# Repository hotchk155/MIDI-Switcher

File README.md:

The old project. Check MIDI-Switcher-2 for new one

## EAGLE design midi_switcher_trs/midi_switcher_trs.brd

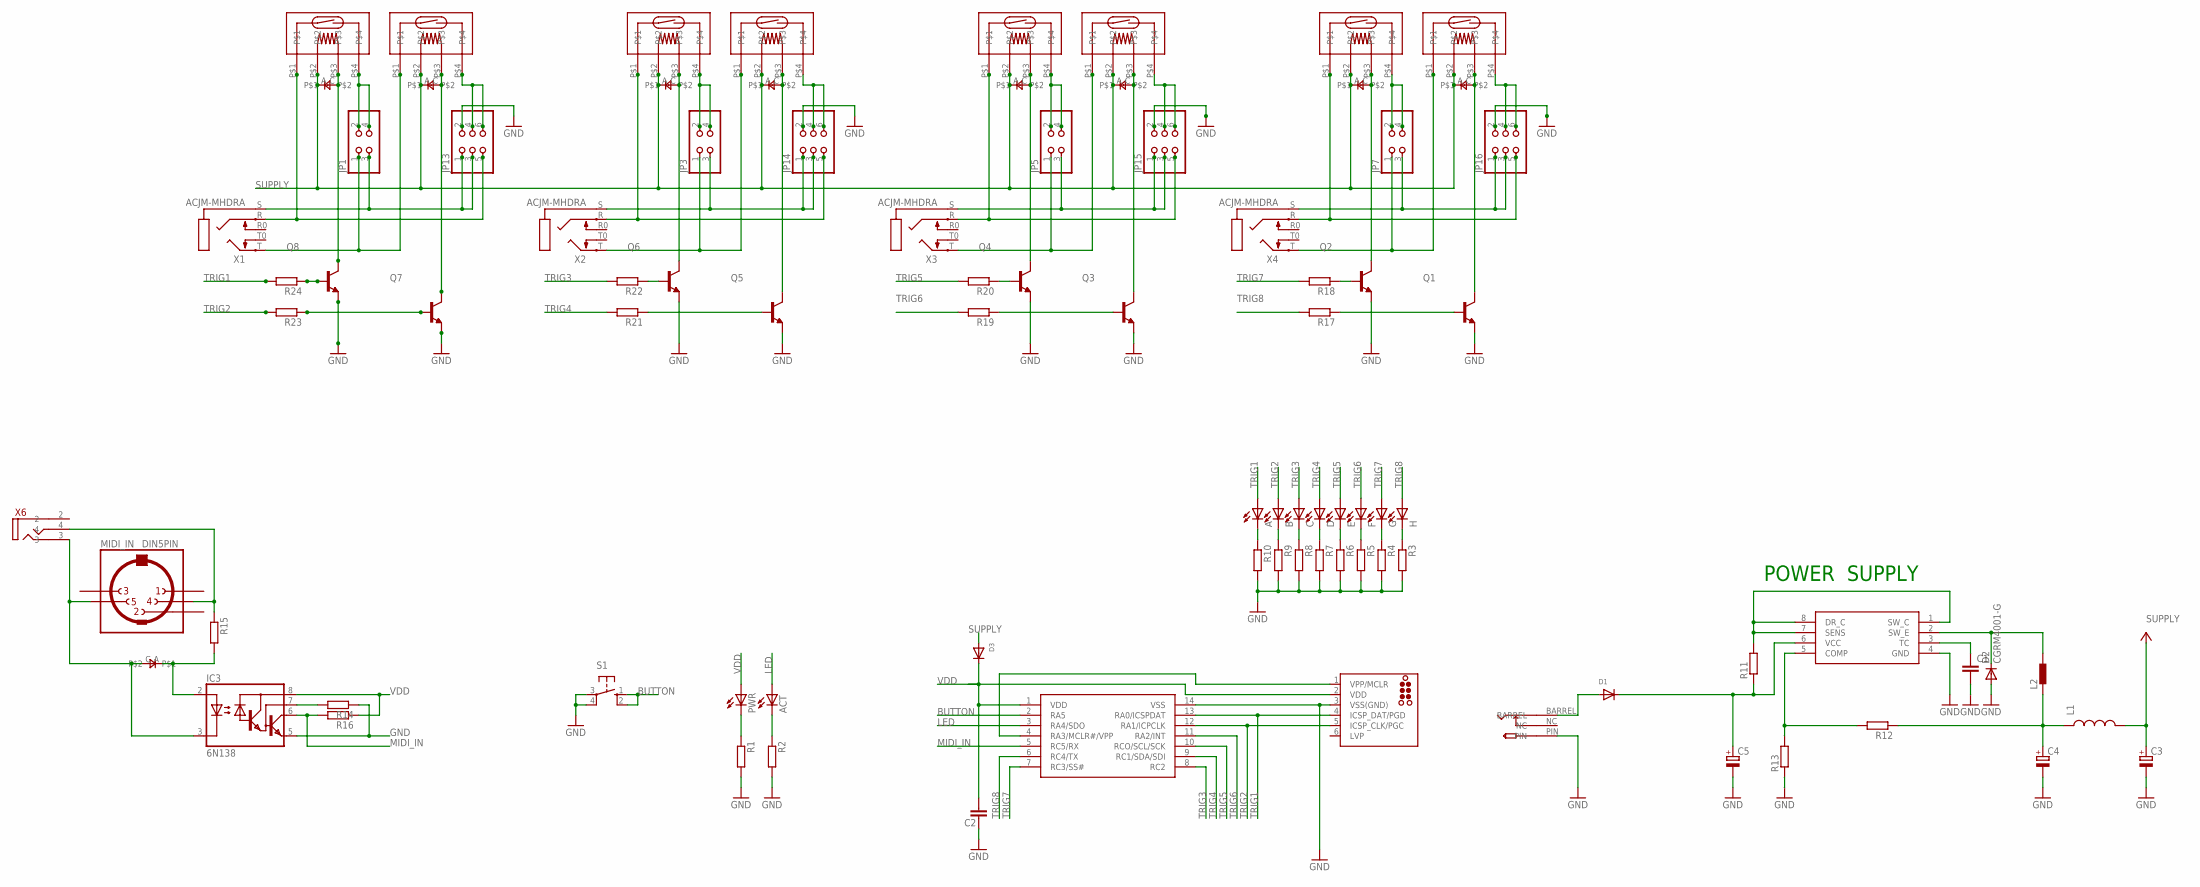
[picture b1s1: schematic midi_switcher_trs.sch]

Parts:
A: LED3MM
ACT: LED3MM
B: LED3MM
C: LED3MM
C1, C2: C-EUC0805; C0805
C3, C4, C5: CPOL-EUE2.5-7; E2,5-7
D: LED3MM
D1, D3: DIODESOD-123; SOD-123
D2: CGRM4001-G; SOD-123_MINI-SMA
D4, D5, D6, D7, D8, D9, D10, D11, D12: 0805DIODE
E: LED3MM
F: LED3MM
G: LED3MM
H: LED3MM
IC1: SP34063A_BOOST_REG; SOIC8
IC2: PIC16F1825SO14; SO14
IC3: 6N138; DIL08
ICSP: TC2030-MCP-NL
JP1, JP3, JP5, JP7: PINHD-2X2; 2X02
JP13, JP14, JP15, JP16: PINHD-2X3; 2X03
L1: INDUCTOR1210; 1210
L2: DR1030
MIDI_IN: DIN5PIN; EDGEDIN
PWR: LED3MM
Q1, Q2, Q3, Q4, Q5, Q6, Q7, Q8: MMBT3904LT1-NPN-SOT23-BEC; SOT23-BEC
R1, R2, R3, R4, R5, R6, R7, R8, R9, R10, R11, R12, R13, R14, R15, R16, R17, R18, R19, R20, R21, R22, R23, R24: R-EU_R0805; R0805
RLY1, RLY2, RLY3, RLY4, RLY5, RLY6, RLY7, RLY8: 9007-REED-RELAY
S1: 10-XX; B3F-10XX
U$9: PWR_SOCKET_2_1MM
X1, X2, X3, X4: ACJM-MHDRA; ACJM-MHDR
X6: VERTICAL_3_5MM_SOCKET

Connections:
+9V: C5.+, D1.C, IC1.6 (VCC), R11.1
BUTTON: IC2.2 (RA5), S1.1 (S), S1.2 (S1)
GND: C1.2, C2.2, C3.-, C4.-, C5.-, D2.A, IC1.4 (GND), IC2.14 (VSS), IC3.5 (GND), ICSP.3 (VSS(GND)), JP13.2, JP14.2, JP15.2, JP16.2, Q1.E, Q2.E, Q3.E, Q4.E, Q5.E, Q6.E, Q7.E, Q8.E, R1.2, R2.2, R3.2, R4.2, R5.2, R6.2, R7.2, R8.2, R9.2, R10.2, R13.1, R14.1, S1.3, S1.4 (P1), U$9.PIN
LED: ACT.A, IC2.3 (RA4/SDO)
MIDI_IN: IC2.5 (RC5/RX), IC3.6 (VO), R16.2
unnamed: JP1.2, JP1.4, RLY1.P$4
unnamed: JP13.4, JP13.6, RLY2.P$4
unnamed: JP13.5, RLY1.P$1, X1.R (2)
unnamed: JP1.1, RLY2.P$1, X1.T (5)
unnamed: JP1.3, JP13.1, JP13.3, X1.S (1)
unnamed: D11.C, Q7.C, RLY2.P$3
unnamed: Q8.B, R24.1
unnamed: Q7.B, R23.1
unnamed: JP3.2, JP3.4, RLY3.P$4
unnamed: D12.C, Q8.C, RLY1.P$3
unnamed: JP14.4, JP14.6, RLY4.P$4
unnamed: JP14.5, RLY3.P$1, X2.R (2)
unnamed: JP3.1, RLY4.P$1, X2.T (5)
unnamed: JP3.3, JP14.1, JP14.3, X2.S (1)
unnamed: D10.C, Q6.C, RLY3.P$3
unnamed: D9.C, Q5.C, RLY4.P$3
unnamed: Q6.B, R22.1
unnamed: Q5.B, R21.1
unnamed: JP5.2, JP5.4, RLY5.P$4
unnamed: JP15.4, JP15.6, RLY6.P$4
unnamed: JP15.5, RLY5.P$1, X3.R (2)
unnamed: JP5.1, RLY6.P$1, X3.T (5)
unnamed: JP5.3, JP15.1, JP15.3, X3.S (1)
unnamed: D8.C, Q4.C, RLY5.P$3
unnamed: D7.C, Q3.C, RLY6.P$3
unnamed: Q4.B, R20.1
unnamed: Q3.B, R19.1
unnamed: JP16.4, JP16.6, RLY8.P$4
unnamed: JP7.2, JP7.4, RLY7.P$4
unnamed: JP16.5, RLY7.P$1, X4.R (2)
unnamed: JP7.1, RLY8.P$1, X4.T (5)
unnamed: JP7.3, JP16.1, JP16.3, X4.S (1)
unnamed: D6.C, Q2.C, RLY7.P$3
unnamed: D5.C, Q1.C, RLY8.P$3
unnamed: Q2.B, R18.1
unnamed: Q1.B, R17.1
unnamed: D4.C, IC3.3 (C), MIDI_IN.5, X6.3
unnamed: MIDI_IN.4, R15.1, X6.4
unnamed: D4.A, IC3.2 (A), R15.2
unnamed: IC3.7 (VB), R14.2
unnamed: PWR.K (C), R1.1
unnamed: D1.A, U$9.BARREL
unnamed: IC1.1 (SW_C), IC1.7 (SENS), IC1.8 (DR_C), R11.2
unnamed: C1.1, IC1.3 (TC)
unnamed: D2.C, IC1.2 (SW_E), L2.2
unnamed: IC1.5 (COMP), R12.2, R13.2
unnamed: ACT.K (C), R2.1
unnamed: A.K (C), R10.1
unnamed: B.K (C), R9.1
unnamed: C.K (C), R8.1
unnamed: D.K (C), R7.1
unnamed: E.K (C), R6.1
unnamed: F.K (C), R5.1
unnamed: G.K (C), R4.1
unnamed: H.K (C), R3.1
unnamed: C4.+, L1.1, L2.1, R12.1
SUPPLY: C3.+, D3.A, D5.A, D6.A, D7.A, D8.A, D9.A, D10.A, D11.A, D12.A, L1.2, RLY1.P$2, RLY2.P$2, RLY3.P$2, RLY4.P$2, RLY5.P$2, RLY6.P$2, RLY7.P$2, RLY8.P$2
TRIG1: A.A, IC2.13 (RA0/ICSPDAT), ICSP.4 (ICSP_DAT/PGD), R24.2
TRIG2: B.A, IC2.12 (RA1/ICPCLK), ICSP.5 (ICSP_CLK/PGC), R23.2
TRIG3: C.A, IC2.8 (RC2), R22.2
TRIG4: D.A, IC2.9 (RC1/SDA/SDI), R21.2
TRIG5: E.A, IC2.10 (RCO/SCL/SCK), R20.2
TRIG6: F.A, IC2.11 (RA2/INT), R19.2
TRIG7: G.A, IC2.7 (RC3/SS#), R18.2
TRIG8: H.A, IC2.6 (RC4/TX), R17.2
VDD: C2.1, D3.C, IC2.1 (VDD), IC3.8 (VCC), ICSP.2 (VDD), PWR.A, R16.1
VPP: IC2.4 (RA3/MCLR#/VPP), ICSP.1 (VPP/MCLR)

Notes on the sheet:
POWER SUPPLY

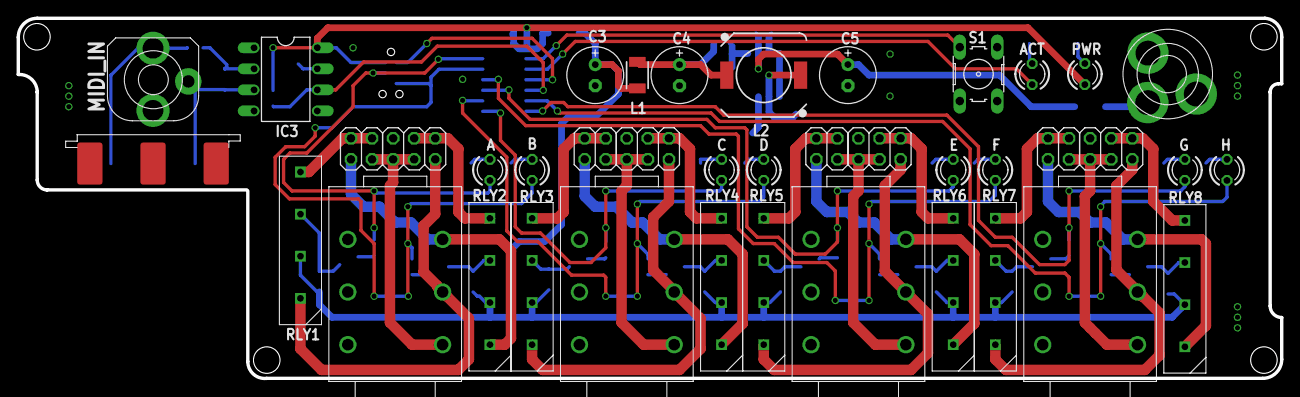
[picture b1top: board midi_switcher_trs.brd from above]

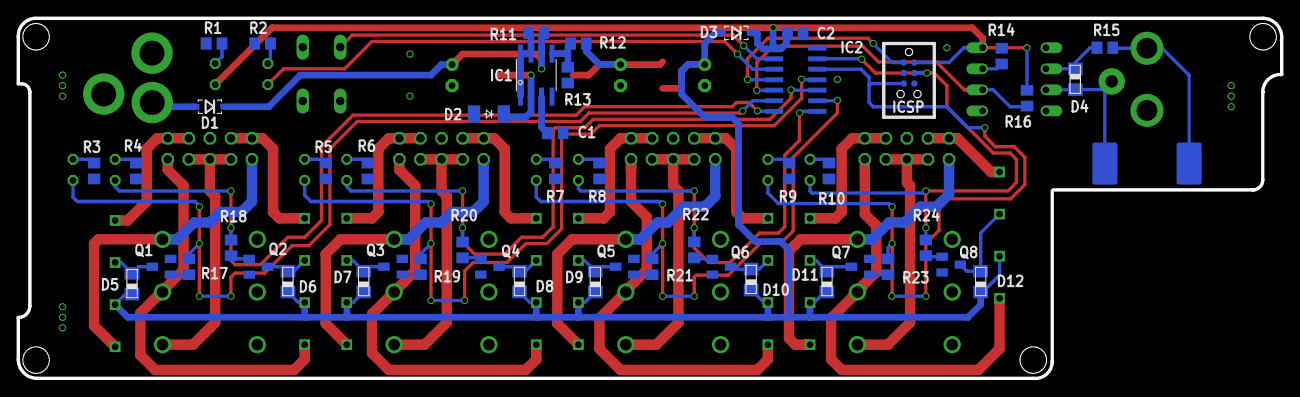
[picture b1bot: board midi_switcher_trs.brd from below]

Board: 2 copper layers, 152.4 x 43.4 mm, 89 parts (49 on the bottom side), 72 nets.

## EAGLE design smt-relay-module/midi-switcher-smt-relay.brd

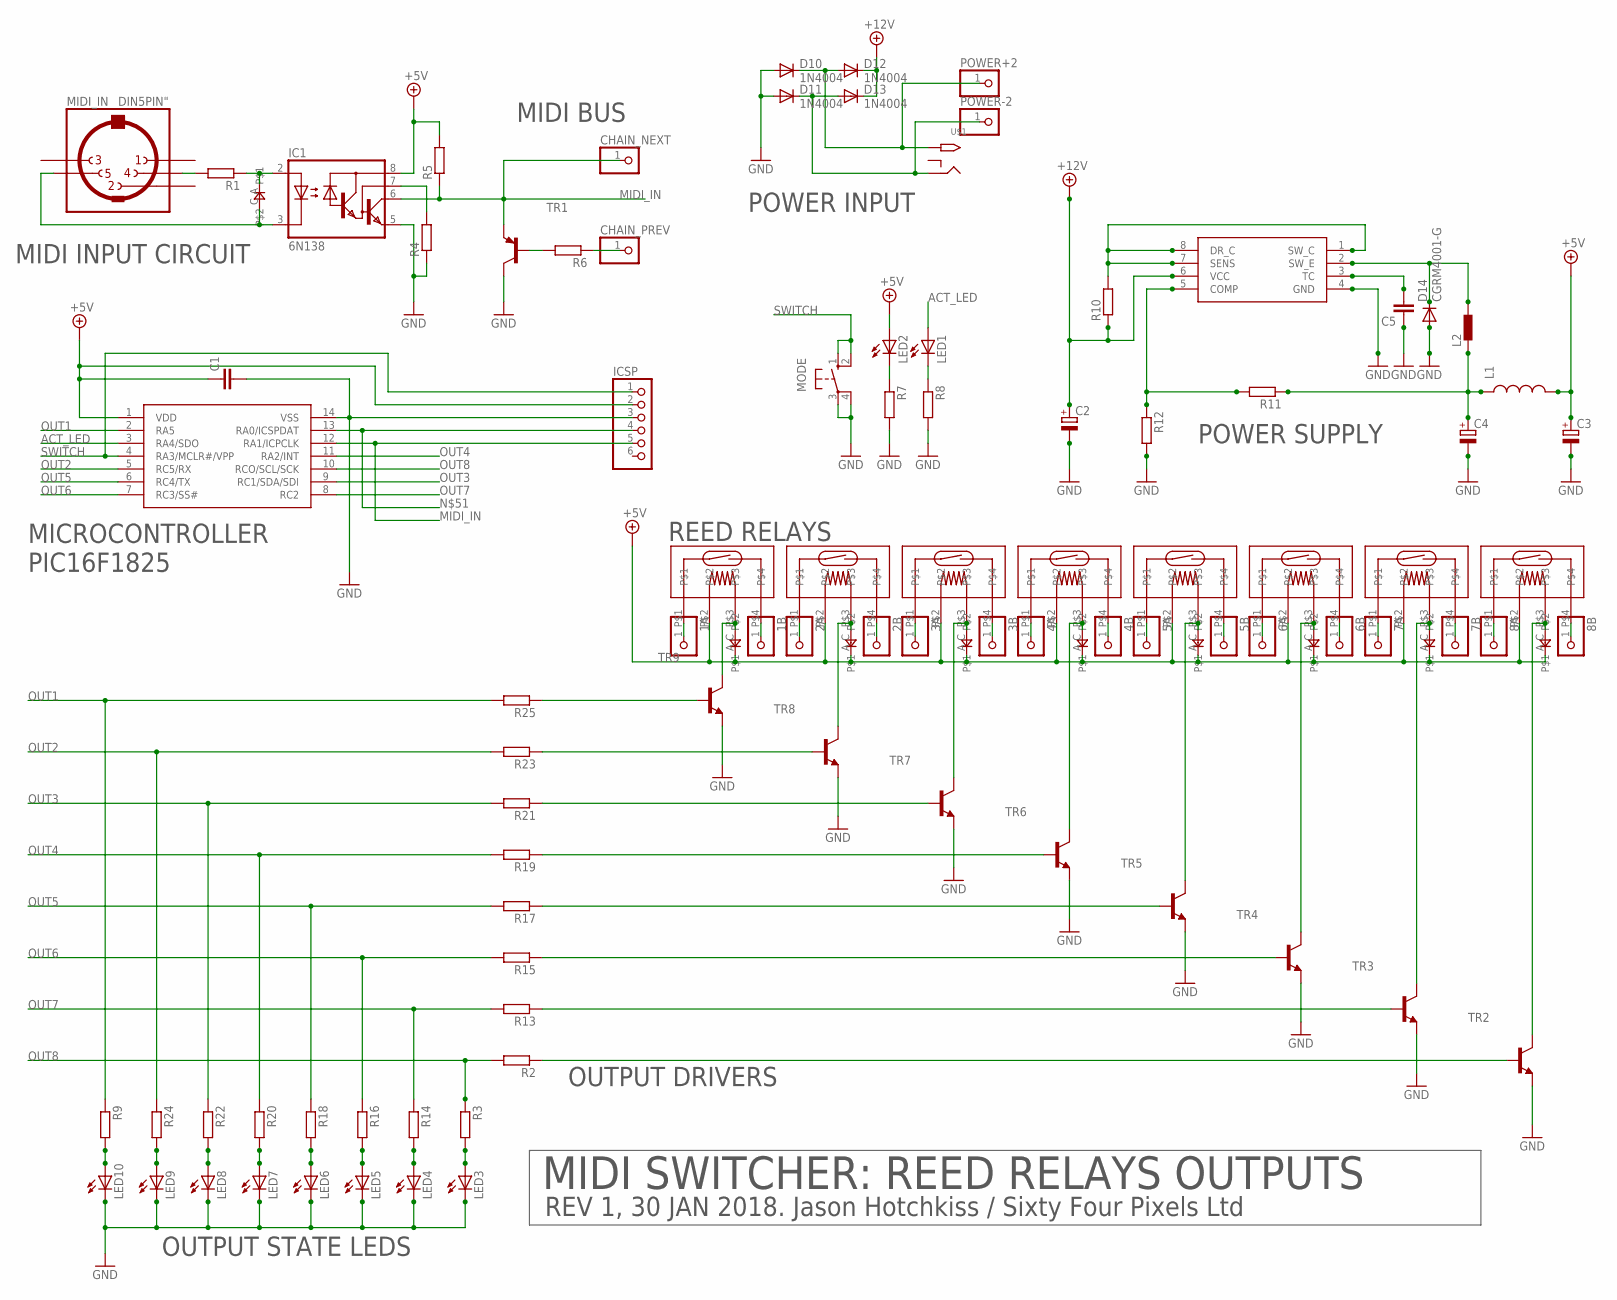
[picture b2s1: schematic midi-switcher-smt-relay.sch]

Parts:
1A, 1B, 2A, 2B, 3A, 3B, 4A, 4B, 5A, 5B, 6A, 6B, 7A, 7B, 8A, 8B: PINHD-1X1; 1X01
C1, C5: C-EUC0805; C0805
C2, C3, C4: CPOL-EUE2.5-7; E2,5-7
CHAIN_NEXT: PINHD-1X1; 1X01
CHAIN_PREV: PINHD-1X1; 1X01
D1, D2, D3, D4, D5, D6, D7, D8, D9: 0805DIODE
D10, D11, D12, D13: 1N4004; DO-VERT
D14: CGRM4001-G; SOD-123_MINI-SMA
IC1: 6N138; DIL08
IC2: PIC16F1825SO14; SO14
IC3: SP34063A_BOOST_REG; SOIC8
ICSP: HEADER-1X6; 1X06_OVAL
L1: INDUCTOR1210; 1210
L2: DR1030
LED1, LED2, LED3, LED4, LED5, LED6, LED7, LED8, LED9, LED10: LEDCHIP-LED0805; CHIP-LED0805
MIDI_IN: DIN5PIN"; TRUCONN90
MODE: 10-XX; B3F-10XX
POWER+2: PINHD-1X1; 1X01
POWER-2: PINHD-1X1; 1X01
R1, R2, R3, R4, R5, R6, R7, R8, R9, R10, R11, R12, R13, R14, R15, R16, R17, R18, R19, R20, R21, R22, R23, R24, R25: R-EU_R0805; R0805
RL1, RL2, RL3, RL4, RL5, RL6, RL7, RL8: 9007-REED-RELAY
TR1: MMBT3906LT1-PNP-SOT23-BEC; SOT23-BEC
TR2, TR3, TR4, TR5, TR6, TR7, TR8, TR9: MMBT3904LT1-NPN-SOT23-BEC; SOT23-BEC
U$1: 2.1MMJACKTHM; PJ-102A

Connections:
+5V: C1.1, C3.+, D2.A, D3.A, D4.A, D5.A, D6.A, D7.A, D8.A, D9.A, IC1.8 (VCC), IC2.1 (VDD), ICSP.2, L1.2, LED2.A, R5.2, RL1.P$2, RL2.P$2, RL3.P$2, RL4.P$2, RL5.P$2, RL6.P$2, RL7.P$2, RL8.P$2
+12V: C2.+, D12.C, D13.C, IC3.6 (VCC), R10.1
ACT_LED: IC2.3 (RA4/SDO), LED1.A
GND: C1.2, C2.-, C3.-, C4.-, C5.1, D10.A, D11.A, D14.A, IC1.5 (GND), IC2.14 (VSS), IC3.4 (GND), ICSP.3, LED3.C, LED4.C, LED5.C, LED6.C, LED7.C, LED8.C, LED9.C, LED10.C, MODE.3, MODE.4 (P1), R4.1, R7.2, R8.2, R12.2, TR1.C, TR2.E, TR3.E, TR4.E, TR5.E, TR6.E, TR7.E, TR8.E, TR9.E
MIDI_IN: CHAIN_NEXT.1, IC1.6 (VO), IC2.12 (RA1/ICPCLK), ICSP.5, R5.1, TR1.E
unnamed: D1.C, IC1.3 (C), MIDI_IN.5
unnamed: MIDI_IN.4, R1.2
unnamed: D1.A, IC1.2 (A), R1.1
unnamed: IC1.7 (VB), R4.2
unnamed: LED1.C, R8.1
unnamed: LED10.A, R9.2
unnamed: LED9.A, R24.2
unnamed: R25.1, TR9.B
unnamed: R23.1, TR8.B
unnamed: R21.1, TR7.B
unnamed: R19.1, TR6.B
unnamed: R17.1, TR5.B
unnamed: R15.1, TR4.B
unnamed: R13.1, TR3.B
unnamed: R2.1, TR2.B
unnamed: R6.2, TR1.B
unnamed: 1A.1, RL8.P$1
unnamed: CHAIN_PREV.1, R6.1
unnamed: 1B.1, RL8.P$4
unnamed: 2A.1, RL7.P$1
unnamed: 2B.1, RL7.P$4
unnamed: 3A.1, RL6.P$1
unnamed: 3B.1, RL6.P$4
unnamed: LED8.A, R22.2
unnamed: 4A.1, RL5.P$1
unnamed: 4B.1, RL5.P$4
unnamed: 5A.1, RL4.P$1
unnamed: LED2.C, R7.1
unnamed: 5B.1, RL4.P$4
unnamed: 6A.1, RL3.P$1
unnamed: 6B.1, RL3.P$4
unnamed: 7A.1, RL2.P$1
unnamed: LED7.A, R20.2
unnamed: 7B.1, RL2.P$4
unnamed: LED6.A, R18.2
unnamed: LED5.A, R16.2
unnamed: LED4.A, R14.2
unnamed: LED3.A, R3.2
unnamed: D11.C, D13.A, POWER-2.1, U$1.RING
unnamed: 8A.1, RL1.P$1
unnamed: 8B.1, RL1.P$4
unnamed: C5.2, IC3.3 (TC)
unnamed: D10.C, D12.A, POWER+2.1, U$1.TIP
unnamed: D9.C, RL8.P$3, TR9.C
unnamed: D8.C, RL7.P$3, TR8.C
unnamed: D7.C, RL6.P$3, TR7.C
unnamed: D6.C, RL5.P$3, TR6.C
unnamed: D5.C, RL4.P$3, TR5.C
unnamed: D4.C, RL3.P$3, TR4.C
unnamed: D3.C, RL2.P$3, TR3.C
unnamed: IC2.13 (RA0/ICSPDAT), ICSP.4
unnamed: D2.C, RL1.P$3, TR2.C
unnamed: D14.C, IC3.2 (SW_E), L2.2
unnamed: C4.+, L1.1, L2.1, R11.1
unnamed: IC3.5 (COMP), R11.2, R12.1
unnamed: IC3.1 (SW_C), IC3.7 (SENS), IC3.8 (DR_C), R10.2
OUT1: IC2.2 (RA5), R9.1, R25.2
OUT2: IC2.5 (RC5/RX), R23.2, R24.1
OUT3: IC2.9 (RC1/SDA/SDI), R21.2, R22.1
OUT4: IC2.11 (RA2/INT), R19.2, R20.1
OUT5: IC2.6 (RC4/TX), R17.2, R18.1
OUT6: IC2.7 (RC3/SS#), R15.2, R16.1
OUT7: IC2.8 (RC2), R13.2, R14.1
OUT8: IC2.10 (RCO/SCL/SCK), R2.2, R3.1
SWITCH: IC2.4 (RA3/MCLR#/VPP), ICSP.1, MODE.1 (S), MODE.2 (S1)

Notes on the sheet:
MIDI INPUT CIRCUIT
MICROCONTROLLER PIC16F1825
POWER SUPPLY
OUTPUT STATE LEDS
OUTPUT DRIVERS
POWER INPUT
MIDI BUS
REED RELAYS
MIDI SWITCHER: REED RELAYS OUTPUTS
REV 1, 30 JAN 2018. Jason Hotchkiss / Sixty Four Pixels Ltd

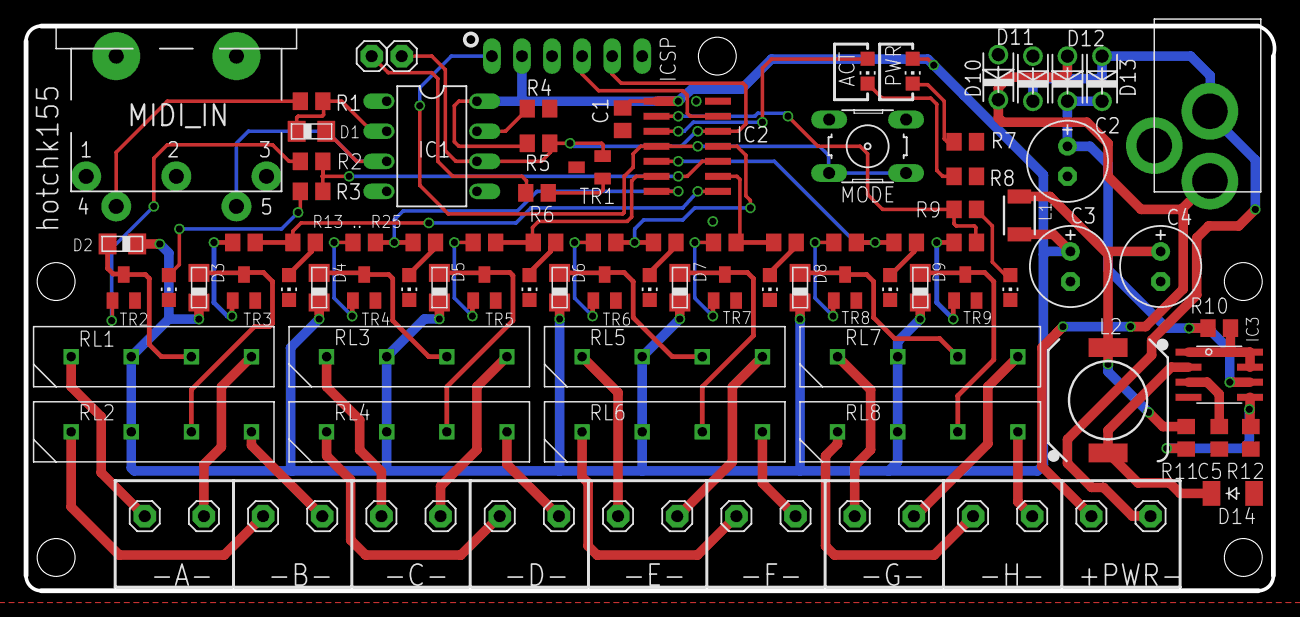
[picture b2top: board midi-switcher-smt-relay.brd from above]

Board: 2 copper layers, 105.5 x 47.7 mm, 100 parts (0 on the bottom side), 70 nets.

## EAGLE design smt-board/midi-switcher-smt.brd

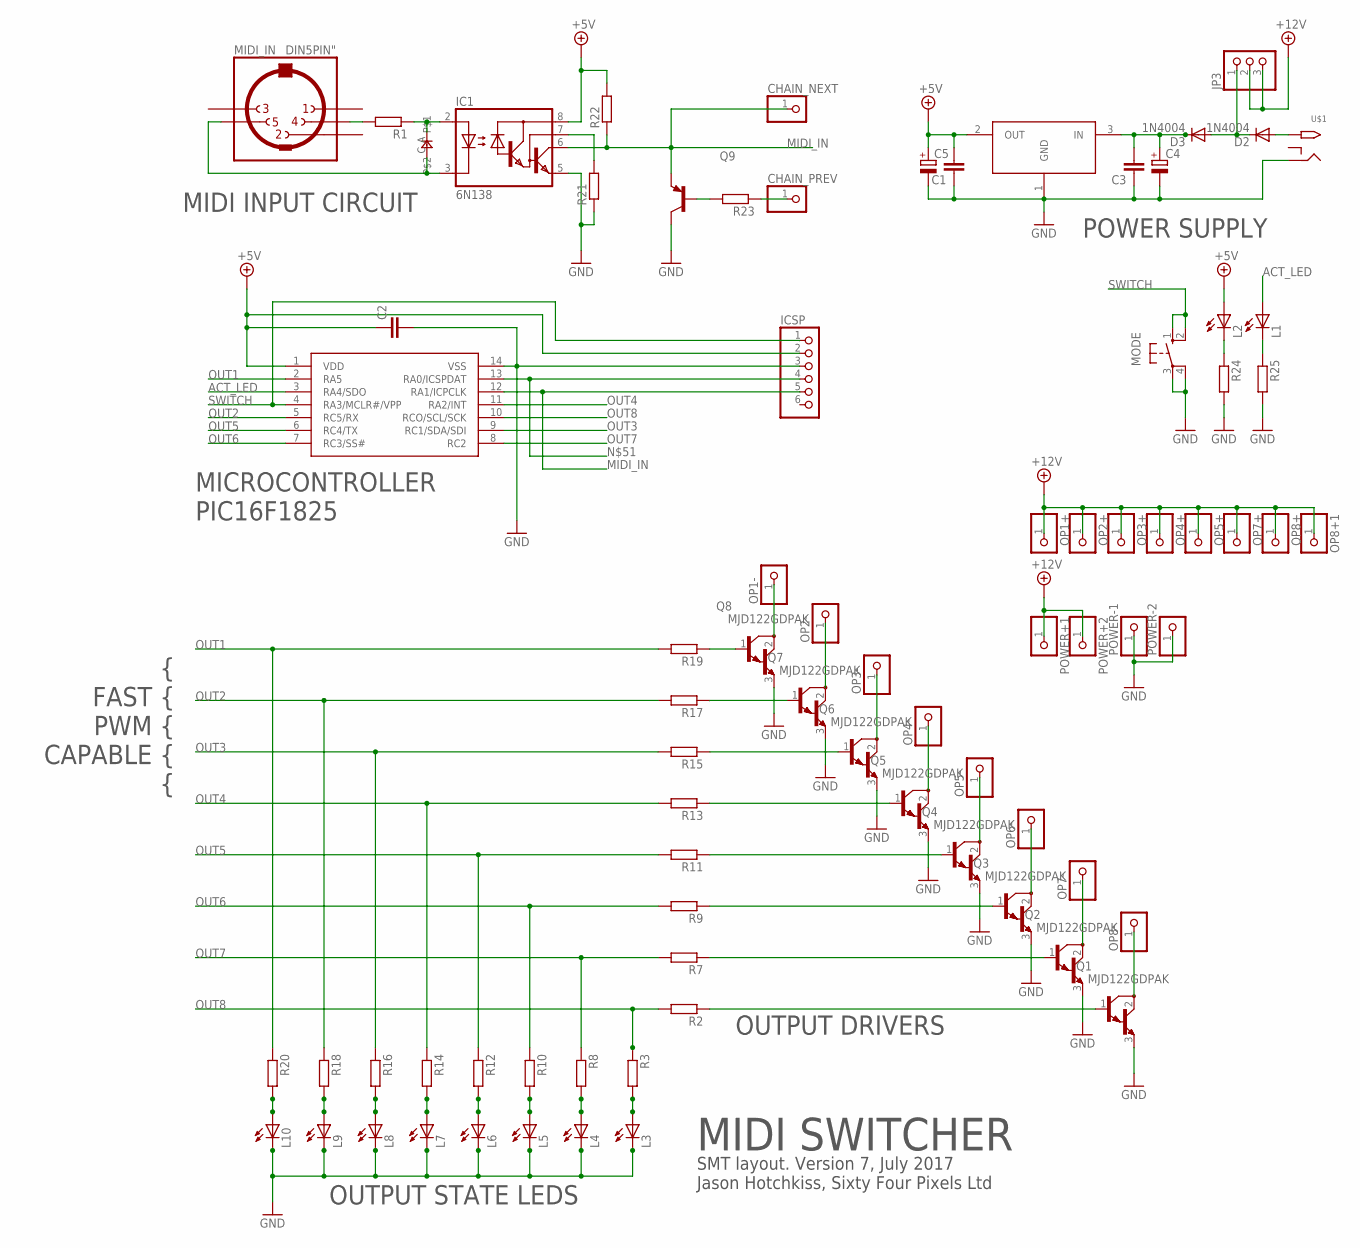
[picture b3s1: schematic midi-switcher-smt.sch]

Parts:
C1, C2, C3: C-EUC0805; C0805
C4: CPOL-EUE2.5-7; E2,5-7
C5: CPOL-EUE2.5-6; E2,5-6
CHAIN_NEXT: PINHD-1X1; 1X01
CHAIN_PREV: PINHD-1X1; 1X01
D1: 0805DIODE
D2, D3: 1N4004; DO-VERT
IC1: 6N138; DIL08
IC2: PIC16F1825SO14; SO14
IC3: LD1086; DPACK
ICSP: HEADER-1X6; 1X06_OVAL
JP3: PINHD-1X3; 1X03
L1, L2, L3, L4, L5, L6, L7, L8, L9, L10: LEDCHIP-LED0805; CHIP-LED0805
MIDI_IN: DIN5PIN"; TRUCONN90
MODE: 10-XX; B3F-10XX
OP1+, OP1-, OP2+, OP2-, OP3+, OP3-, OP4+, OP4-, OP5+, OP5-, OP6-, OP7+, OP7-, OP8+, OP8+1, OP8-: PINHD-1X1; 1X01
POWER+1, POWER+2: PINHD-1X1; 1X01
POWER-1, POWER-2: PINHD-1X1; 1X01
Q1, Q2, Q3, Q4, Q5, Q6, Q7, Q8: MJD122GDPAK; DPACK
Q9: MMBT3906LT1-PNP-SOT23-BEC; SOT23-BEC
R1, R2, R3, R7, R8, R9, R10, R11, R12, R13, R14, R15, R16, R17, R18, R19, R20, R21, R22, R23, R24, R25: R-EU_R0805; R0805
U$1: 2.1MMJACKTHM; PJ-102A

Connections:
+5V: C1.2, C2.1, C5.+, IC1.8 (VCC), IC2.1 (VDD), IC3.2 (OUT), ICSP.2, L2.A, R22.2
+12V: JP3.2, JP3.3, OP1+.1, OP2+.1, OP3+.1, OP4+.1, OP5+.1, OP7+.1, OP8+.1, OP8+1.1, POWER+1.1, POWER+2.1
ACT_LED: IC2.3 (RA4/SDO), L1.A
GND: C1.1, C2.2, C3.1, C4.-, C5.-, IC1.5 (GND), IC2.14 (VSS), IC3.1 (GND), ICSP.3, L3.C, L4.C, L5.C, L6.C, L7.C, L8.C, L9.C, L10.C, MODE.3, MODE.4 (P1), POWER-1.1, POWER-2.1, Q1.3 (E), Q2.3 (E), Q3.3 (E), Q4.3 (E), Q5.3 (E), Q6.3 (E), Q7.3 (E), Q8.3 (E), Q9.C, R21.1, R24.2, R25.2, U$1.RING
MIDI_IN: CHAIN_NEXT.1, IC1.6 (VO), IC2.12 (RA1/ICPCLK), ICSP.5, Q9.E, R22.1
unnamed: D1.C, IC1.3 (C), MIDI_IN.5
unnamed: MIDI_IN.4, R1.2
unnamed: D1.A, IC1.2 (A), R1.1
unnamed: IC1.7 (VB), R21.2
unnamed: L1.C, R25.1
unnamed: L10.A, R20.2
unnamed: L9.A, R18.2
unnamed: Q8.1 (B), R19.1
unnamed: Q7.1 (B), R17.1
unnamed: Q6.1 (B), R15.1
unnamed: Q5.1 (B), R13.1
unnamed: Q4.1 (B), R11.1
unnamed: Q3.1 (B), R9.1
unnamed: Q2.1 (B), R7.1
unnamed: Q1.1 (B), R2.1
unnamed: Q9.B, R23.2
unnamed: CHAIN_PREV.1, R23.1
unnamed: L8.A, R16.2
unnamed: OP1-.1, Q8.2 (C)
unnamed: OP2-.1, Q7.2 (C)
unnamed: OP3-.1, Q6.2 (C)
unnamed: L2.C, R24.1
unnamed: OP5-.1, Q4.2 (C)
unnamed: OP6-.1, Q3.2 (C)
unnamed: OP4-.1, Q5.2 (C)
unnamed: L7.A, R14.2
unnamed: L6.A, R12.2
unnamed: L5.A, R10.2
unnamed: L4.A, R8.2
unnamed: L3.A, R3.2
unnamed: C3.2, C4.+, D3.C, IC3.3 (IN)
unnamed: OP7-.1, Q2.2 (C)
unnamed: D2.A, U$1.TIP
unnamed: OP8-.1, Q1.2 (C)
unnamed: IC2.13 (RA0/ICSPDAT), ICSP.4
unnamed: D2.C, D3.A, JP3.1
OUT1: IC2.2 (RA5), R19.2, R20.1
OUT2: IC2.5 (RC5/RX), R17.2, R18.1
OUT3: IC2.9 (RC1/SDA/SDI), R15.2, R16.1
OUT4: IC2.11 (RA2/INT), R13.2, R14.1
OUT5: IC2.6 (RC4/TX), R11.2, R12.1
OUT6: IC2.7 (RC3/SS#), R9.2, R10.1
OUT7: IC2.8 (RC2), R7.2, R8.1
OUT8: IC2.10 (RCO/SCL/SCK), R2.2, R3.1
SWITCH: IC2.4 (RA3/MCLR#/VPP), ICSP.1, MODE.1 (S), MODE.2 (S1)

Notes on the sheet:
MIDI SWITCHER
SMT layout. Version 7, July 2017 Jason Hotchkiss, Sixty Four Pixels Ltd
MIDI INPUT CIRCUIT
MICROCONTROLLER PIC16F1825
POWER SUPPLY
OUTPUT STATE LEDS
OUTPUT DRIVERS
{ FAST { PWM { CAPABLE { {

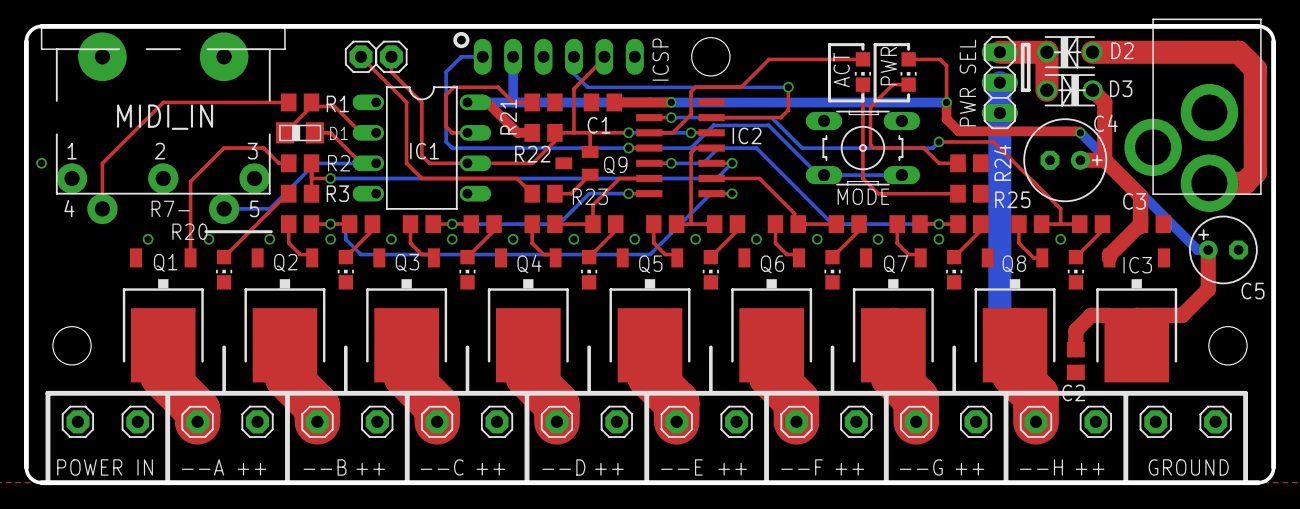
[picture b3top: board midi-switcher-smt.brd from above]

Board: 2 copper layers, 104.1 x 38.1 mm, 79 parts (0 on the bottom side), 50 nets.

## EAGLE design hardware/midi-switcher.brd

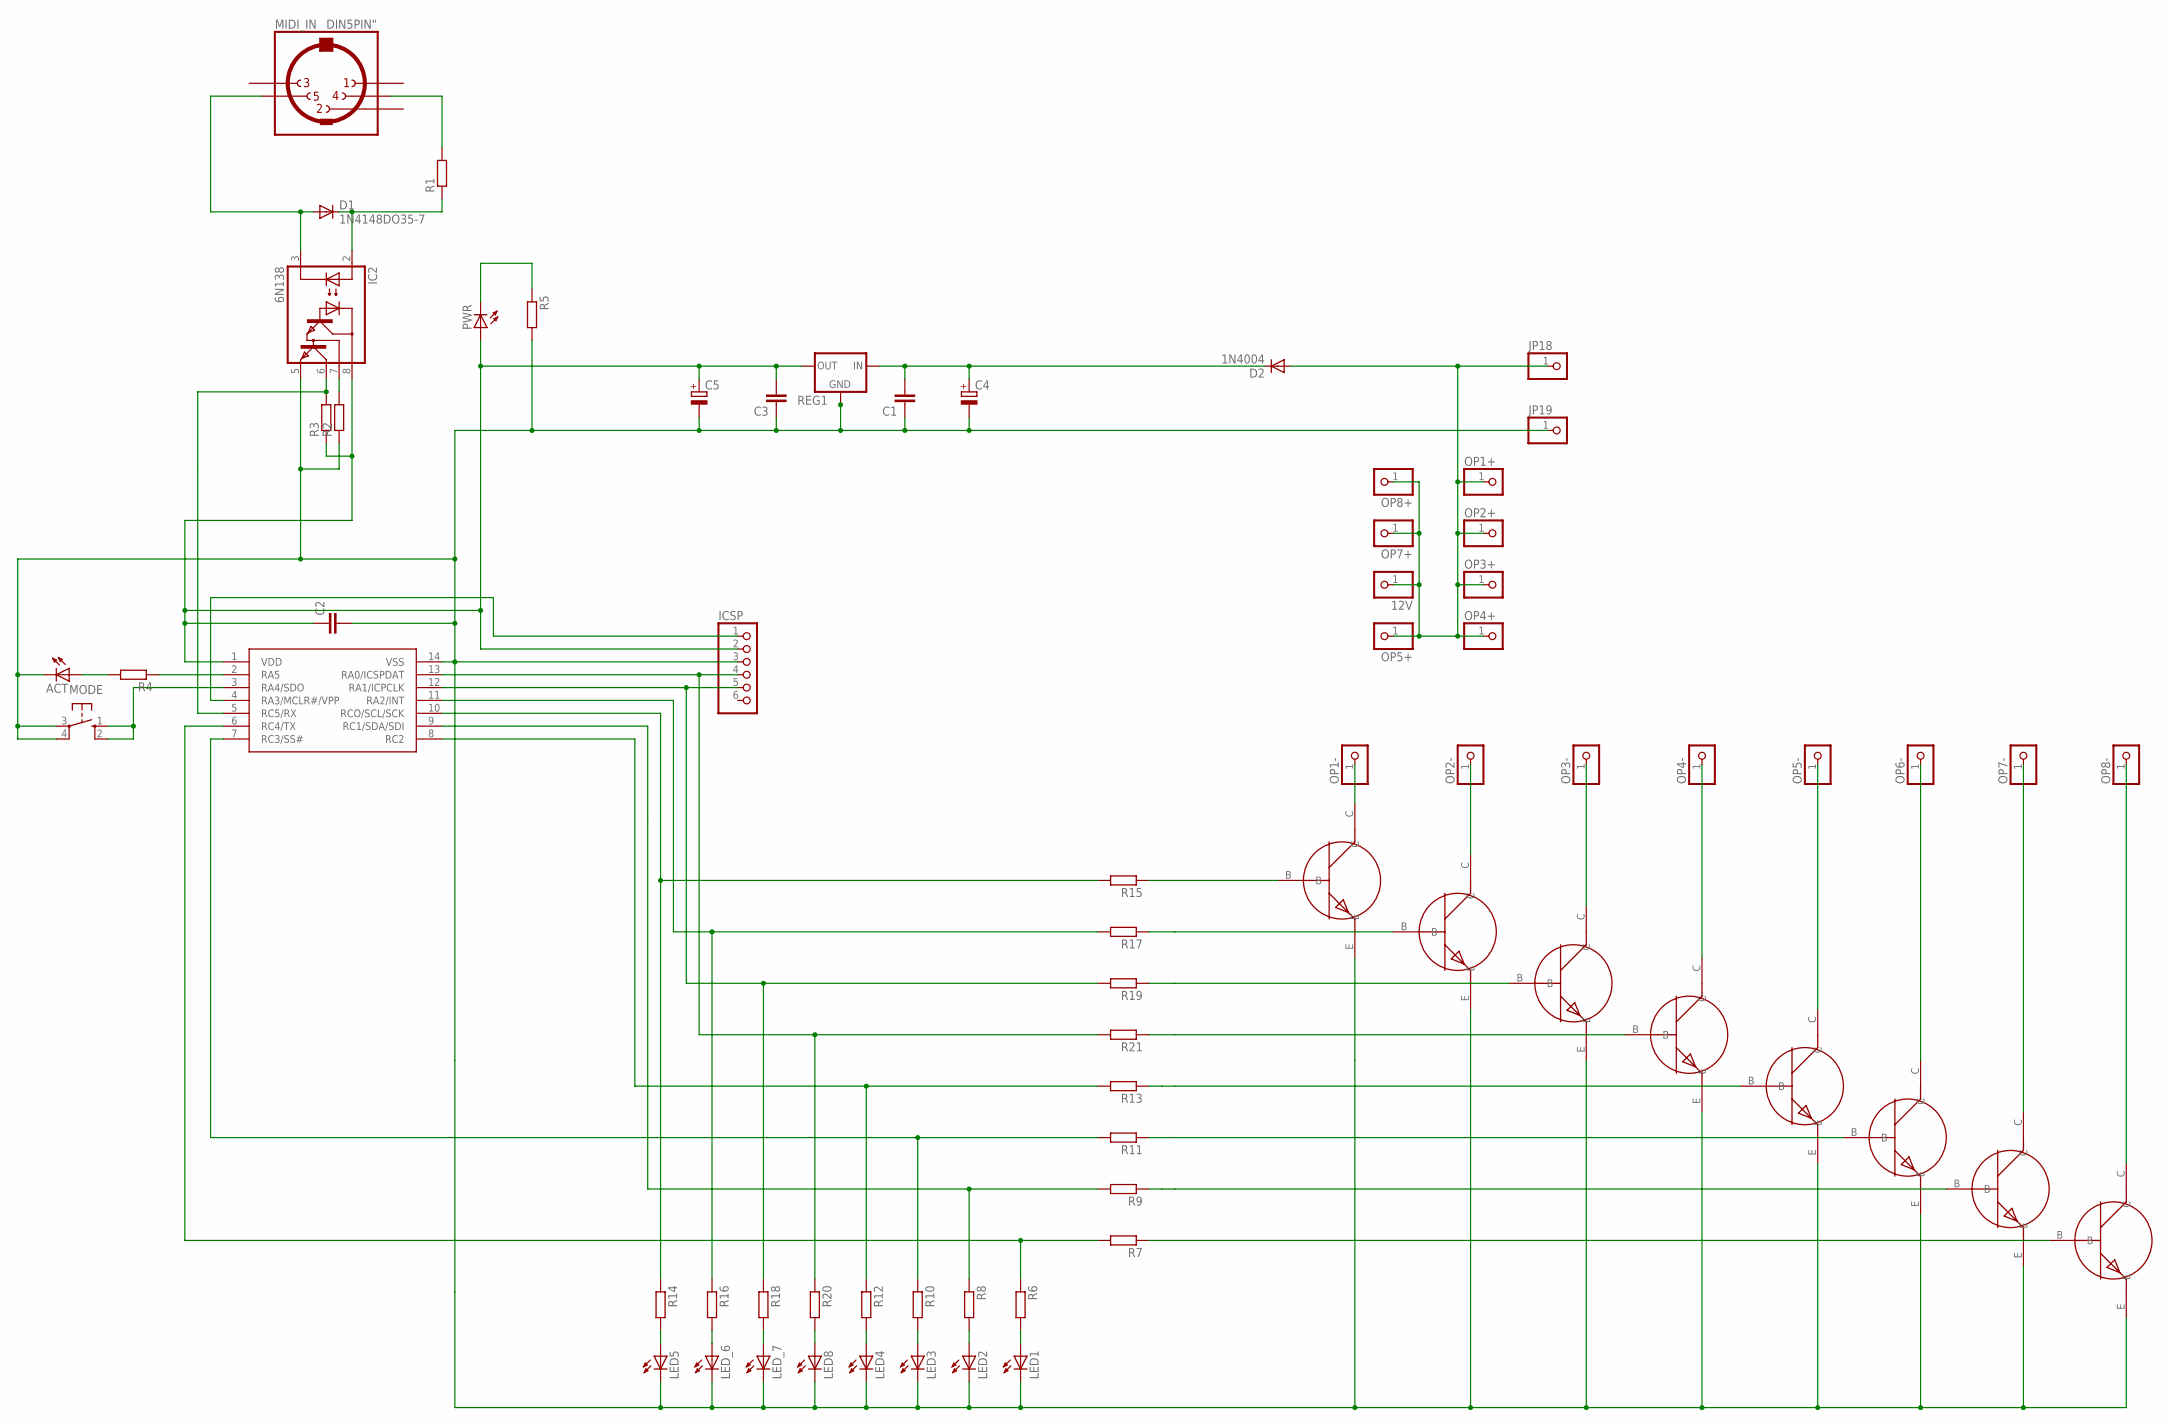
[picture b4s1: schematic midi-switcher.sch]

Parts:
12V: PINHD-1X1; 1X01
ACT: LED3MM
C1, C2, C3: C-EU025-025X050; C025-025X050
C4, C5: CPOL-EUE2.5-7; E2,5-7
D1: 1N4148DO35-7; DO35-7
D2: 1N4004; DO41-10
IC1: PIC16F1825DIL14; DIL14
IC2: 6N138; DIL08
ICSP: HEADER-1X6; 1X06_OVAL
JP18, JP19: PINHD-1X1; 1X01
LED1, LED2, LED3, LED4, LED5, LED8: LED3MM
LED_6, LED_7: LED3MM
MIDI_IN: DIN5PIN"; TRUCONN90
MODE: 10-XX; B3F-10XX
OP1+, OP1-, OP2+, OP2-, OP3+, OP3-, OP4+, OP4-, OP5+, OP5-, OP6-, OP7+, OP7-, OP8+, OP8-: PINHD-1X1; 1X01
PWR: LED3MM
R1, R2, R3, R4, R5, R6, R7, R8, R9, R10, R11, R12, R13, R14, R15, R16, R17, R18, R19, R20, R21: R-EU_0207/7; 0207/7
REG1: 78XXS
U$1, U$2, U$3, U$4, U$5, U$6, U$7, U$8: TIP120

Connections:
12V: 12V.1, D2.A, JP18.1, OP1+.1, OP2+.1, OP3+.1, OP4+.1, OP5+.1, OP7+.1, OP8+.1
GND: ACT.K (C), C1.1, C2.2, C3.1, C4.-, C5.-, IC1.14 (VSS), IC2.5 (GND), ICSP.3, JP19.1, LED1.K (C), LED2.K (C), LED3.K (C), LED4.K (C), LED5.K (C), LED8.K (C), LED_6.K (C), LED_7.K (C), MODE.3, MODE.4 (P1), R2.1, R5.2, REG1.GND, U$1.E, U$2.E, U$3.E, U$4.E, U$5.E, U$6.E, U$7.E, U$8.E
unnamed: MIDI_IN.4, R1.2
unnamed: D1.C, IC2.2 (A), R1.1
unnamed: D1.A, IC2.3 (C), MIDI_IN.5
unnamed: IC2.7 (VB), R2.2
unnamed: ACT.A, R4.2
unnamed: LED5.A, R14.2
unnamed: LED_6.A, R16.2
unnamed: R15.1, U$1.B
unnamed: R17.1, U$2.B
unnamed: R19.1, U$4.B
unnamed: R21.1, U$3.B
unnamed: R13.1, U$5.B
unnamed: R11.1, U$6.B
unnamed: R9.1, U$7.B
unnamed: R7.1, U$8.B
unnamed: IC1.5 (RC5/RX), IC2.6 (VO), R3.2
unnamed: IC1.2 (RA5), R4.1
unnamed: IC1.12 (RA1/ICPCLK), ICSP.5, R18.1, R19.2
unnamed: IC1.13 (RA0/ICSPDAT), ICSP.4, R20.1, R21.2
unnamed: IC1.8 (RC2), R12.1, R13.2
unnamed: IC1.7 (RC3/SS#), R10.1, R11.2
unnamed: IC1.9 (RC1/SDA/SDI), R8.1, R9.2
unnamed: IC1.6 (RC4/TX), R6.1, R7.2
unnamed: LED_7.A, R18.2
unnamed: OP1-.1, U$1.C
unnamed: OP2-.1, U$2.C
unnamed: OP3-.1, U$4.C
unnamed: OP5-.1, U$5.C
unnamed: OP6-.1, U$6.C
unnamed: OP4-.1, U$3.C
unnamed: LED8.A, R20.2
unnamed: IC1.4 (RA3/MCLR#/VPP), ICSP.1
unnamed: LED4.A, R12.2
unnamed: LED3.A, R10.2
unnamed: LED2.A, R8.2
unnamed: LED1.A, R6.2
unnamed: C1.2, C4.+, D2.C, REG1.IN
unnamed: PWR.K (C), R5.1
unnamed: OP7-.1, U$7.C
unnamed: IC1.3 (RA4/SDO), MODE.1 (S), MODE.2 (S1)
unnamed: IC1.11 (RA2/INT), R16.1, R17.2
unnamed: IC1.10 (RCO/SCL/SCK), R14.1, R15.2
unnamed: OP8-.1, U$8.C
VDD: C2.1, C3.2, C5.+, IC1.1 (VDD), IC2.8 (VCC), ICSP.2, PWR.A, R3.1, REG1.OUT

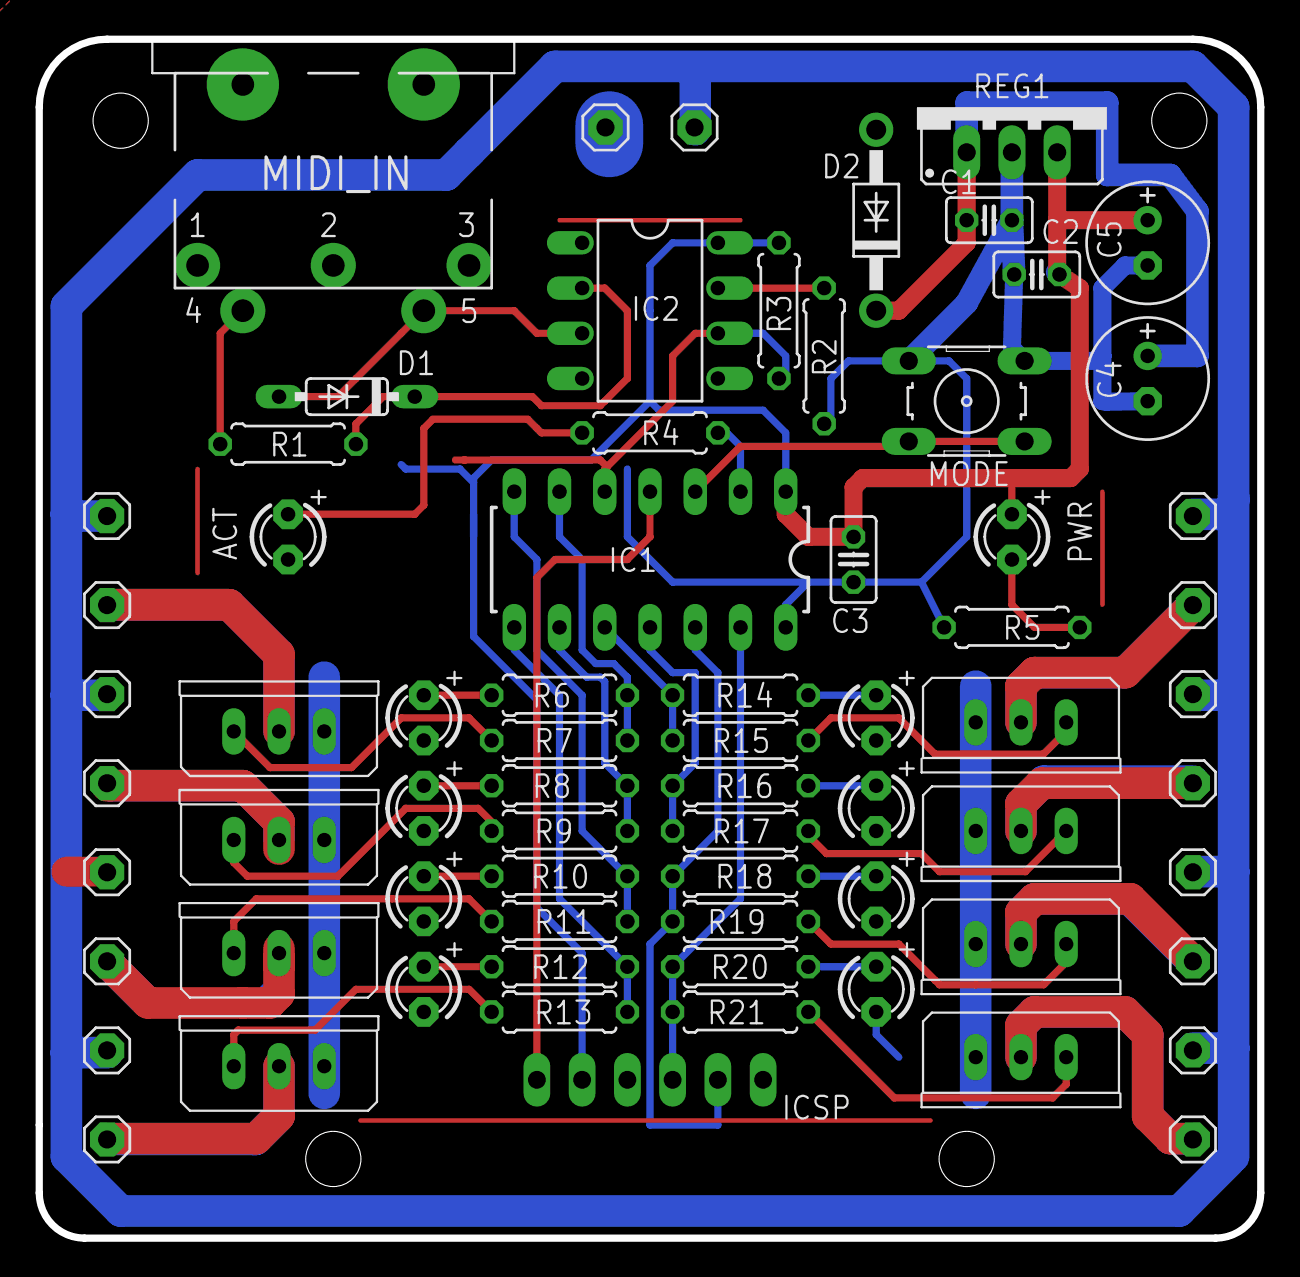
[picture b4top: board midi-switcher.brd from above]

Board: 2 copper layers, 68.6 x 67.3 mm, 70 parts (0 on the bottom side), 46 nets.

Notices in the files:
parts and their libraries:
tag-connect: ©2009 ROFA.cz - modified and updated by Robert Darlington ‹rdarlington@gmail.com›
